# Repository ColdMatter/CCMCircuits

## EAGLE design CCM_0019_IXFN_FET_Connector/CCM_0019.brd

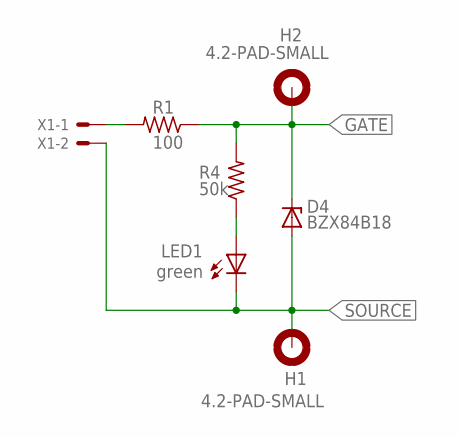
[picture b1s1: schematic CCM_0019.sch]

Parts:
D4: BZX84B18; SOT23
H1, H2: 4.2-PAD-SMALL
LED1: green; CHIPLED_0603
R1: 100; 0603
R4: 50k; 0603
X1: 22-23-2021

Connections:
GATE: D4.3 (C), H2.B4,2, R1.1, R4.2
unnamed: LED1.A, R4.1
unnamed: R1.2, X1.1
SOURCE: D4.1 (A), H1.B4,2, LED1.C, X1.2

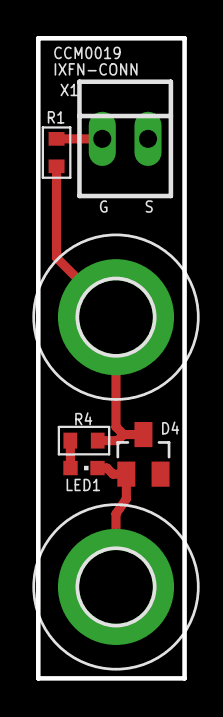
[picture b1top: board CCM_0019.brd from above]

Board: 2 copper layers, 8.1 x 35.6 mm, 7 parts (0 on the bottom side), 4 nets.

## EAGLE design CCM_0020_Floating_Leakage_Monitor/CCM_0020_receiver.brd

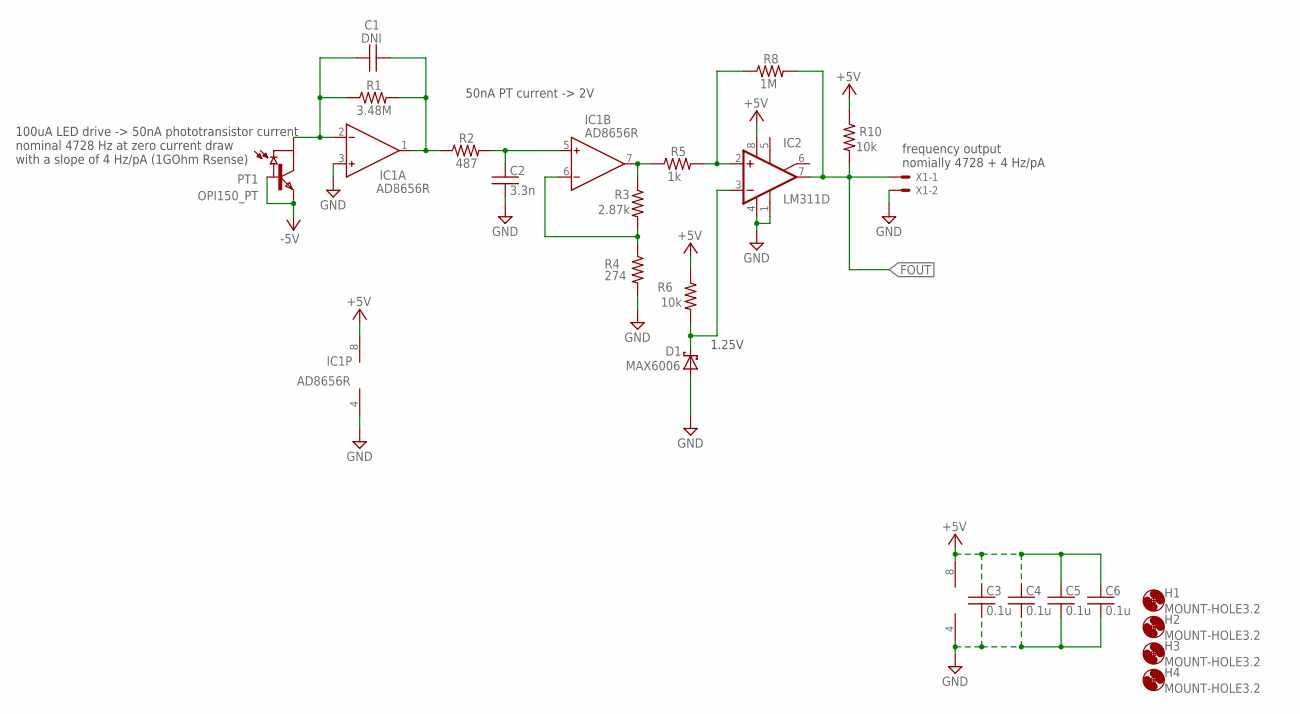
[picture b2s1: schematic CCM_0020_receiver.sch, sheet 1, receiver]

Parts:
C1: DNI; 0603
C2: 3.3n; 0603
C3, C4, C5, C6: 0.1u; 0603
D1: MAX6006; SOT23
H1, H2, H3, H4: MOUNT-HOLE3.2; 3,2
IC1: AD8656R; SO8
IC2: LM311D; SO08
IC3: LT1495; SO08
PT1: OPI150_PT; OPI150_PHOTOTRANSISTOR
R1: 3.48M; 0603
R2: 487; 0603
R3: 2.87k; 0603
R4: 274; 0603
R5: 1k; 0603
R6, R10: 10k; 0603
R8: 1M; 0603
X1: 22-23-2021

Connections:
+5V: C3.1, C4.1, C5.1, C6.1, IC1.8 (V+), IC2.8 (V+), IC3.8 (V+), R6.1, R10.1; also elsewhere on the board
-5V: PT1.P4 (BASE), PT1.P5 (EMITTER)
FOUT: IC2.7 (OUT), R8.2, R10.2, X1.1; also elsewhere on the board
GND: C2.2, C3.2, C4.2, C5.2, C6.2, D1.2 (A), IC1.3 (IN+), IC1.4 (V-), IC2.1 (GND), IC2.4 (V-), IC3.4 (V-), R4.2, X1.2; also elsewhere on the board
unnamed: C1.1, IC1.2 (IN-), PT1.P3 (COLLECTOR), R1.1
unnamed: C2.1, IC1.5 (IN+), R2.2
unnamed: C1.2, IC1.1 (OUT), R1.2, R2.1
unnamed: IC1.6 (IN-), R3.2, R4.1
unnamed: IC1.7 (OUT), R3.1, R5.1
unnamed: IC2.2 (+IN), R5.2, R8.1
unnamed: D1.1 (C), IC2.3 (-IN), R6.2

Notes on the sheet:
100uA LED drive -> 50nA phototransistor current nominal 4728 Hz at zero current draw with a slope of 4 Hz/pA (1GOhm Rsense)
50nA PT current -> 2V
1.25V
frequency output nomially 4728 + 4 Hz/pA

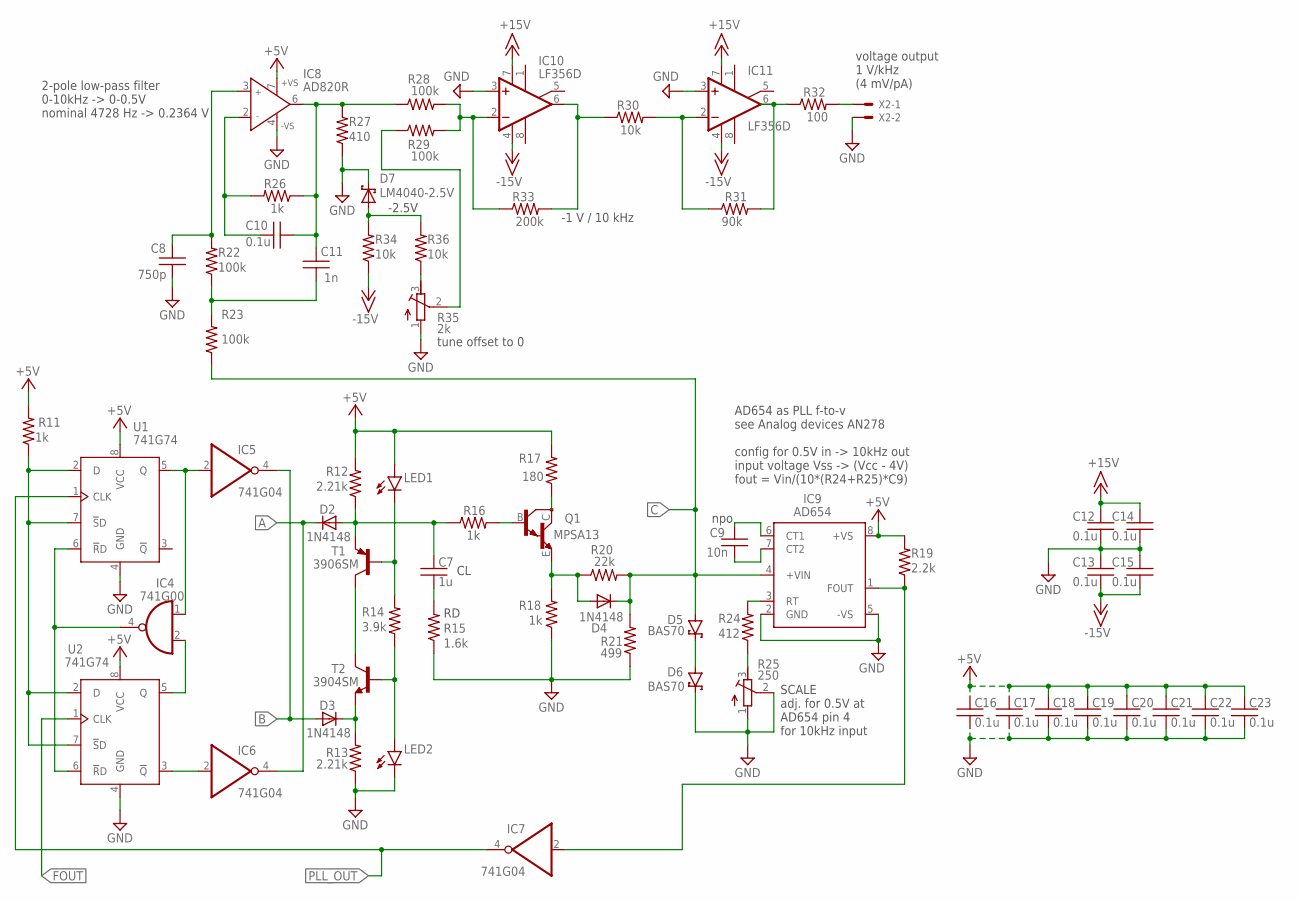
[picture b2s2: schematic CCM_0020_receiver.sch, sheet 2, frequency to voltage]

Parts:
C7: 1u; 0603
C8: 750p; 0603
C9: 10n; 0603
C10, C12, C13, C14, C15, C16, C17, C18, C19, C20, C21, C22, C23: 0.1u; 0603
C11: 1n; 0603
D2, D3, D4: 1N4148; SOD323_ST
D5, D6: BAS70; SOT23
D7: LM4040-2.5V; SOT23
IC4: 741G00; SOT23-5
IC5, IC6, IC7: 741G04; SOT23-5
IC8: AD820R; SO8
IC9: AD654; SO08
IC10, IC11: LF356D; SO08
LED1, LED2: LEDCHIP-LED0603; CHIP-LED0603
Q1: MPSA13; SOT23-BEC
R11, R16, R18, R26: 1k; 0603
R12, R13: 2.21k; 0603
R14: 3.9k; 0603
R15: 1.6k; 0603
R17: 180; 0603
R19: 2.2k; 0603
R20: 22k; 0603
R21: 499; 0603
R22, R23, R28, R29: 100k; 0603
R24: 412; 0603
R25: 250; RTRIM64Y
R27: 410; 0603
R30, R34, R36: 10k; 0603
R31: 90k; 0603
R32: 100; 0603
R33: 200k; 0603
R35: 2k; RTRIM64Y
T1: 3906SM; SOT23-BEC
T2: 3904SM; SOT23
U1, U2: 741G74; TSSOP8
X2: 22-23-2021

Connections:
+5V: C16.1, C17.1, C18.1, C19.1, C20.1, C21.1, C22.1, C23.1, IC8.7 (+VS), IC9.8 (+VS), LED1.A, R11.2, R12.2, R17.2, R19.2, U1.8 (VCC), U2.8 (VCC); also elsewhere on the board
+15V: C12.2, C14.2, IC10.7 (V+), IC11.7 (V+)
-15V: C13.1, C15.1, IC10.4 (V-), IC11.4 (V-), R34.1
A: D2.C, IC6.4 (O)
B: D3.A, IC5.4 (O)
C: D4.C, D5.1 (A), IC9.4 (+VIN), R20.2, R21.2, R23.1
FOUT: U2.1 (CLK); also elsewhere on the board
GND: C8.1, C12.1, C13.2, C14.1, C15.2, C16.2, C17.2, C18.2, C19.2, C20.2, C21.2, C22.2, C23.2, D6.3 (C), D7.1 (C), IC4.3 (GND), IC5.3 (GND), IC6.3 (GND), IC7.3 (GND), IC8.4 (-VS), IC9.2 (GND), IC9.5 (-VS), IC10.3 (+IN), IC11.3 (+IN), LED2.C, R13.1, R15.1, R18.1, R21.1, R25.1 (A), R25.2 (S), R27.1, R35.1 (A), U1.4 (GND), U2.4 (GND), X2.2; also elsewhere on the board
unnamed: C9.1, IC9.6 (CT1)
unnamed: IC4.4 (O), U1.6 (!R!D), U2.6 (!R!D)
unnamed: IC4.2 (I1), U2.5 (Q)
unnamed: R11.1, U1.2 (D), U1.7 (!S!D), U2.2 (D), U2.7 (!S!D)
unnamed: IC6.2 (I), U2.3 (!Q)
unnamed: C11.1, R22.1, R23.2
unnamed: IC4.1 (I0), IC5.2 (I), U1.5 (Q)
unnamed: C8.2, IC8.3 (IN+), R22.2
unnamed: C9.2, IC9.7 (CT2)
unnamed: R24.1, R25.3 (E)
unnamed: D5.3 (C), D6.1 (A)
unnamed: C7.1, D2.A, R12.1, R16.1, T1.E
unnamed: D3.C, R13.2, T2.2 (E)
unnamed: T1.C, T2.3 (C)
unnamed: LED1.C, R14.2, T1.B
unnamed: LED2.A, R14.1, T2.1 (B)
unnamed: C7.2, R15.2
unnamed: Q1.C, R17.1
unnamed: Q1.B, R16.2
unnamed: D4.A, Q1.E, R18.2, R20.1
unnamed: IC9.3 (RT), R24.2
unnamed: IC7.2 (I), IC9.1 (FOUT), R19.1
unnamed: C10.2, C11.2, IC8.6 (OUT), R26.1, R27.2, R28.1
unnamed: C10.1, IC8.2 (IN-), R26.2
unnamed: IC10.2 (-IN), R28.2, R29.2, R33.1
unnamed: IC11.6 (OUT), R31.2, R32.1
unnamed: IC11.2 (-IN), R30.2, R31.1
unnamed: R32.2, X2.1
unnamed: IC10.6 (OUT), R30.1, R33.2
unnamed: D7.2 (A), R34.2, R36.2
unnamed: R29.1, R35.2 (S)
unnamed: R35.3 (E), R36.1
PLL_OUT: IC7.4 (O), U1.1 (CLK)
VCC: IC4.5 (VCC), IC5.5 (VCC), IC6.5 (VCC), IC7.5 (VCC)

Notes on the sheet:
npo
SCALE adj. for 0.5V at AD654 pin 4 for 10kHz input
2-pole low-pass filter 0-10kHz -> 0-0.5V nominal 4728 Hz -> 0.2364 V
AD654 as PLL f-to-v see Analog devices AN278 config for 0.5V in -> 10kHz out input voltage Vss -> (Vcc - 4V) fout = Vin/(10*(R24+R25)*C9)
-2.5V
tune offset to 0
-1 V / 10 kHz
voltage output 1 V/kHz (4 mV/pA)

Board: 2 copper layers, 89 parts (0 on the bottom side), 50 nets, no tracks yet.

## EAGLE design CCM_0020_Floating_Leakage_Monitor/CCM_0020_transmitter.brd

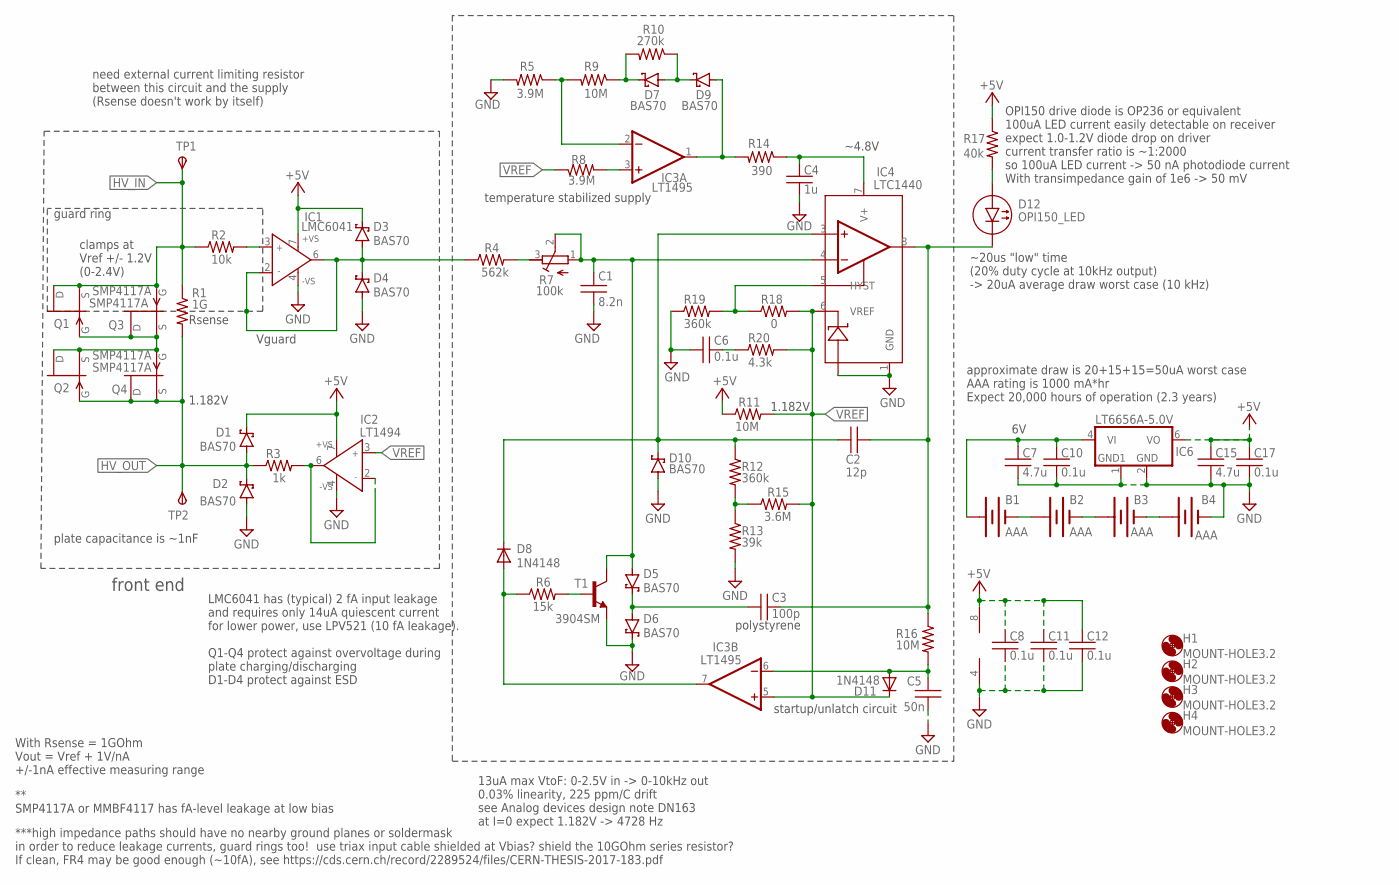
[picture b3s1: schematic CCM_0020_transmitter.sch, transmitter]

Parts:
B1, B2, B3, B4: AAA; AAA_SM
C1: 8.2n; 0603
C2: 12p; 0603
C3: 100p; 0603
C4: 1u; 0603
C5: 50n; 0603
C6, C8, C10, C11, C12, C17: 0.1u; 0603
C7, C15: 4.7u; 0603
D1, D2, D3, D4, D5, D6, D7, D9, D10: BAS70; SOT23
D8, D11: 1N4148; SOD323_ST
D12: OPI150_LED
H1, H2, H3, H4: MOUNT-HOLE3.2; 3,2
IC1: LMC6041; SO08
IC2: LT1494; SO08
IC3: LT1495; SO08
IC4: LTC1440; SO8
IC6: LT6656A-5.0V; SOT23-6
Q1, Q2, Q3, Q4: SMP4117A; SOT23
R1: 1G; 2512
R2: 10k; 0603
R3: 1k; 0603
R4: 562k; 0603
R5, R8: 3.9M; 0603
R6: 15k; 0603
R7: 100k; RTRIM64Y
R9, R11, R16: 10M; 0603
R10: 270k; 0603
R12, R19: 360k; 0603
R13: 39k; 0603
R14: 390; 0603
R15: 3.6M; 0603
R17: 40k; 0603
R18: 0; 0603
R20: 4.3k; 0603
T1: 3904SM; SOT23
TP1, TP2: TPSPAD1-17; P1-17

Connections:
+5V: C8.1, C11.1, C12.1, C15.1, C17.1, D1.3 (C), D3.3 (C), IC1.7 (+VS), IC2.7 (+VS), IC3.8 (V+), IC6.6 (VO), R11.1, R17.1
GND: B4.-, C1.2, C4.2, C5.2, C6.1, C7.2, C8.2, C10.2, C11.2, C12.2, C15.2, C17.2, D2.1 (A), D4.1 (A), D6.3 (C), D10.1 (A), IC1.4 (-VS), IC2.4 (-VS), IC3.4 (V-), IC4.1 (GND), IC4.2 (V-), IC6.1 (GND1), IC6.2 (GND), R5.2, R13.2, R19.1, T1.2 (E)
HV_IN: Q1.1 (D), Q1.2 (S), Q3.3 (G), R1.1, R2.1, TP1.TP
HV_IN1: Q1.3 (G), Q2.1 (D), Q2.2 (S), Q3.1 (D), Q3.2 (S), Q4.3 (G)
HV_OUT: D1.1 (A), D2.3 (C), Q2.3 (G), Q4.1 (D), Q4.2 (S), R1.2, R3.1, TP2.TP
unnamed: D3.1 (A), D4.3 (C), IC1.2 (IN-), IC1.6 (OUT), R4.1
unnamed: IC4.5 (HYST), R18.1, R19.2
unnamed: D12.P$1 (1(A)), R17.2
unnamed: B1.-, B2.+
unnamed: C6.2, R20.1
unnamed: C5.1, D11.A, IC3.6 (-IN), R16.2
unnamed: IC1.3 (IN+), R2.2
unnamed: R4.2, R7.3 (E)
unnamed: C1.1, D5.1 (A), IC4.4 (-IN), R7.1 (A), R7.2 (S), T1.3 (C)
unnamed: C3.1, D5.3 (C), D6.1 (A)
unnamed: R6.2, T1.1 (B)
unnamed: D8.A, IC3.7 (OUT), R6.1
unnamed: R12.2, R13.1, R15.1
unnamed: C2.1, D8.C, D10.3 (C), IC4.3 (+IN), R12.1
unnamed: D7.1 (A), D9.3 (C), R10.1
unnamed: D7.3 (C), R9.1, R10.2
unnamed: IC3.2 (-IN), R5.1, R9.2
unnamed: B1.+, C7.1, C10.1, IC6.4 (VI)
unnamed: D9.1 (A), IC3.1 (OUT), R14.2
unnamed: C4.1, IC4.7 (V+), R14.1
unnamed: IC3.3 (+IN), R8.2
unnamed: B2.-, B3.+
unnamed: B3.-, B4.+
unnamed: IC2.2 (IN-), IC2.6 (OUT), R3.2
VREF: D11.C, IC2.3 (IN+), IC3.5 (+IN), IC4.6 (VREF), R8.1, R11.2, R15.2, R18.2, R20.2
VTOF_OUTPUT: C2.2, C3.2, D12.P$2 (2(C)), IC4.8 (OUT), R16.1

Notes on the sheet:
** SMP4117A or MMBF4117 has fA-level leakage at low bias
plate capacitance is ~1nF
With Rsense = 1GOhm Vout = Vref + 1V/nA +/-1nA effective measuring range
***high impedance paths should have no nearby ground planes or soldermask in order to reduce leakage currents, guard rings too! use triax input cable shielded at Vbias? shield the 10GOhm series resistor? If clean, FR4 may be good enough (~10fA), see https://cds.cern.ch/record/2289524/files/CERN-THE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
polystyrene
front end
13uA max VtoF: 0-2.5V in -> 0-10kHz out 0.03% linearity, 225 ppm/C drift see Analog devices design note DN163 at I=0 expect 1.182V -> 4728 Hz
1.182V
clamps at Vref +/- 1.2V (0-2.4V)
approximate draw is 20+15+15=50uA worst case AAA rating is 1000 mA*hr Expect 20,000 hours of operation (2.3 years)
guard ring
~20us "low" time (20% duty cycle at 10kHz output) -> 20uA average draw worst case (10 kHz)
OPI150 drive diode is OP236 or equivalent 100uA LED current easily detectable on receiver expect 1.0-1.2V diode drop on driver current transfer ratio is ~1:2000 so 100uA LED current -> 50 nA photodiode current With transimpedance gain of 1e6 -> 50 mV
Vguard
LMC6041 has (typical) 2 fA input leakage and requires only 14uA quiescent current for lower power, use LPV521 (10 fA leakage). Q1-Q4 protect against overvoltage during plate charging/discharging D1-D4 protect against ESD
need external current limiting resistor between this circuit and the supply (Rsense doesn't work by itself)
Rsense
temperature stabilized supply
startup/unlatch circuit
~4.8V

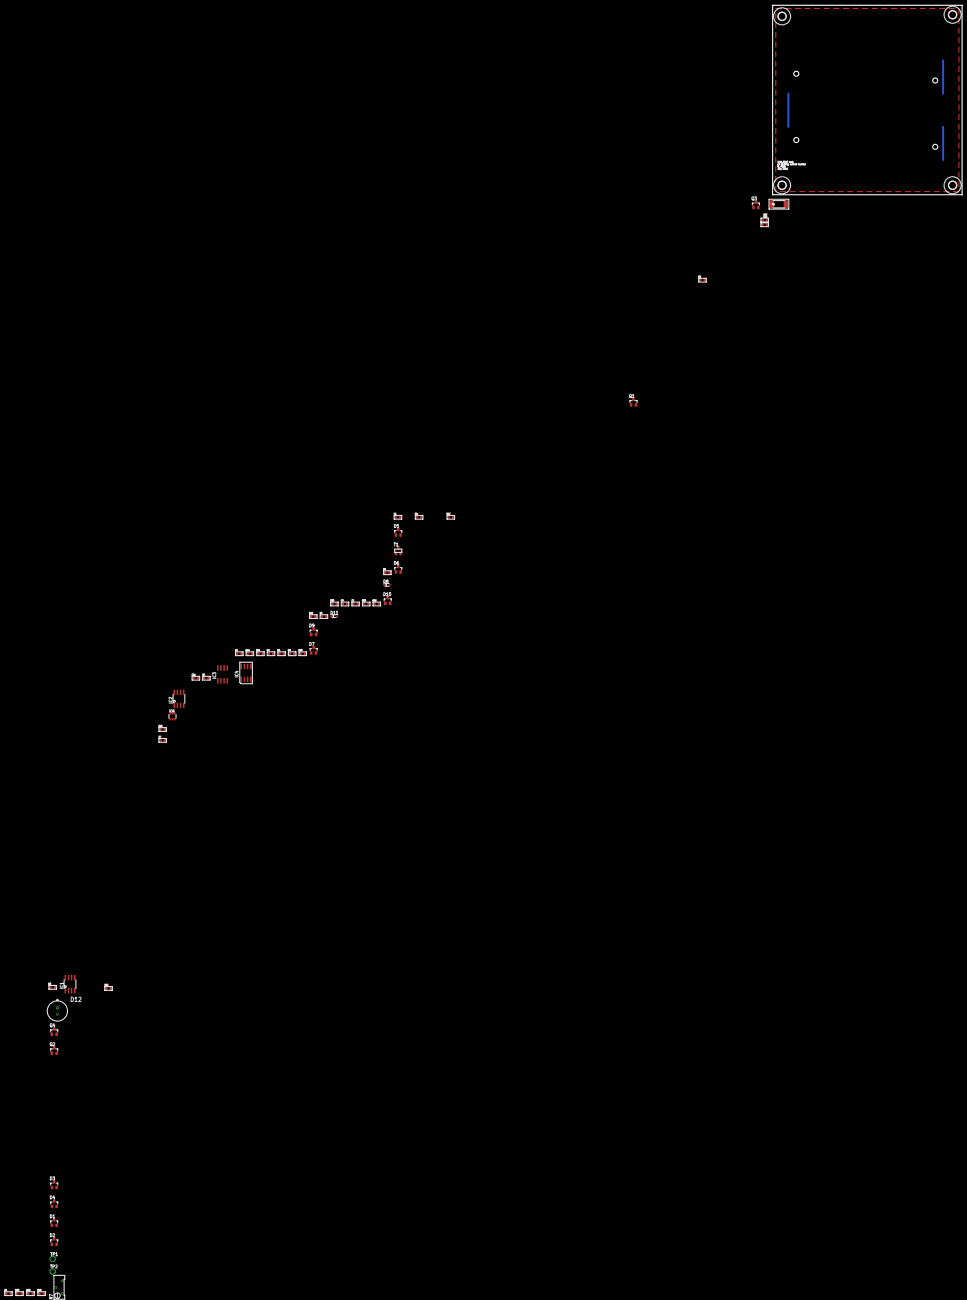
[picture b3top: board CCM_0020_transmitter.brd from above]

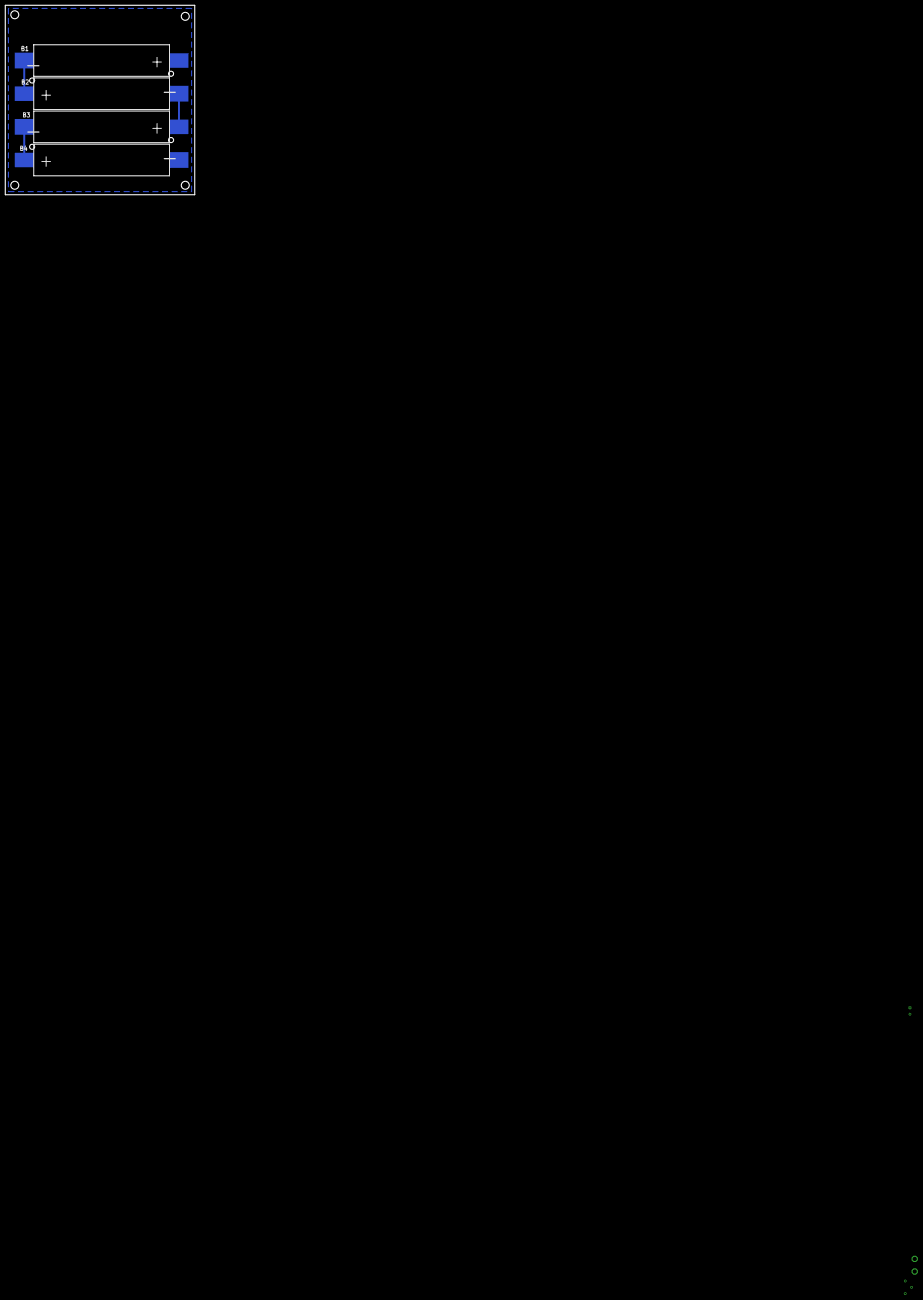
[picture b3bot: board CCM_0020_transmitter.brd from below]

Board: 2 copper layers, 76.2 x 76.2 mm, 65 parts (4 on the bottom side), 31 nets.

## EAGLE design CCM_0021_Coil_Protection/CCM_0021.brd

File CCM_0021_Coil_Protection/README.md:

# CCM_0021 Coil Protection
     
This circuit is designed to provide some level of protection for coils, particularly useful for those installed in vacuum where a melted coil represents a serious annoyance.  It features an adjustable soft current limit (by clamping a control voltage) and an adjustable hard energy limit (by opening an interlock and disabling the power supply).  The latter feature is obtained by integrating the dissipated power (roughly) and comparing to a setpoint.  

## Design Resources

## Design Notes

## Known Issues

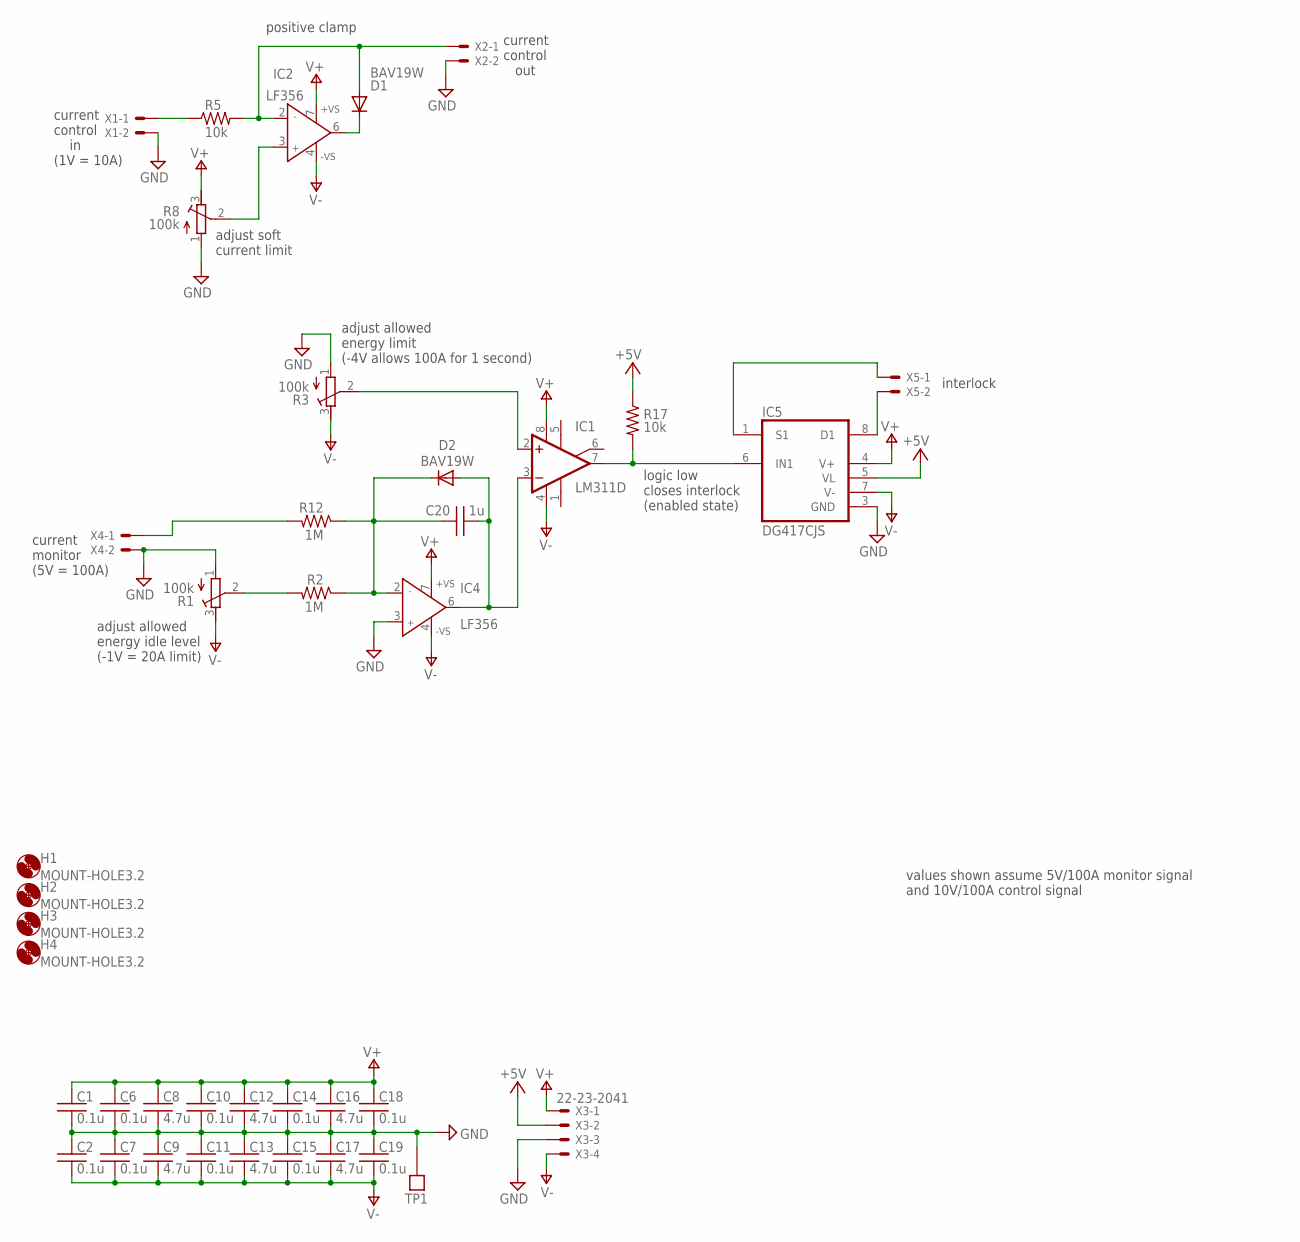
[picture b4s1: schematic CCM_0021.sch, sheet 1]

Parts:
C1, C2, C6, C7, C10, C11, C14, C15, C18, C19: 0.1u; 0603
C8, C9, C12, C13, C16, C17: 4.7u; 0603
C20: 1u; 0603
D1, D2: BAV19W; SOD123
H1, H2, H3, H4: MOUNT-HOLE3.2; 3,2
IC1: LM311D; SO08
IC2, IC4: LF356; SO8
IC5: DG417CJS; SO8
R1, R3, R8: 100k; RTRIM3296W
R2, R12: 1M; 0603
R5, R17: 10k; 0603
TP1: TESTPOINT
X1, X2, X4, X5: 22-23-2021
X3: 22-23-2041

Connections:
+5V: IC5.5 (VL), R17.1, X3.2
GND: C1.2, C2.1, C6.2, C7.1, C8.2, C9.1, C10.2, C11.1, C12.2, C13.1, C14.2, C15.1, C16.2, C17.1, C18.2, C19.1, IC4.3 (IN+), IC5.3 (GND), R1.1 (A), R3.1 (A), R8.1 (A), TP1.P$1, X1.2, X2.2, X3.3, X4.2
unnamed: R12.2, X4.1
unnamed: R1.2 (S), R2.2
unnamed: C20.1, D2.A, IC1.3 (-IN), IC4.6 (OUT)
unnamed: IC1.2 (+IN), R3.2 (S)
unnamed: IC1.7 (OUT), IC5.6 (IN1), R17.2
unnamed: IC5.1 (S1), X5.1
unnamed: IC5.8 (D1), X5.2
unnamed: D1.C, IC2.6 (OUT)
unnamed: IC2.3 (IN+), R8.2 (S)
unnamed: R5.1, X1.1
unnamed: D1.A, IC2.2 (IN-), R5.2, X2.1
unnamed: C20.2, D2.C, IC4.2 (IN-), R2.1, R12.1
V+: C1.1, C6.1, C8.1, C10.1, C12.1, C14.1, C16.1, C18.1, IC1.8 (V+), IC2.7 (+VS), IC4.7 (+VS), IC5.4 (V+), R8.3 (E), X3.1
V-: C2.2, C7.2, C9.2, C11.2, C13.2, C15.2, C17.2, C19.2, IC1.4 (V-), IC2.4 (-VS), IC4.4 (-VS), IC5.7 (V-), R1.3 (E), R3.3 (E), X3.4

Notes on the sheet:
current control in (1V = 10A)
positive clamp
adjust soft current limit
current control out
current monitor (5V = 100A)
adjust allowed energy idle level (-1V = 20A limit)
values shown assume 5V/100A monitor signal and 10V/100A control signal
adjust allowed energy limit (-4V allows 100A for 1 second)
interlock
logic low closes interlock (enabled state)

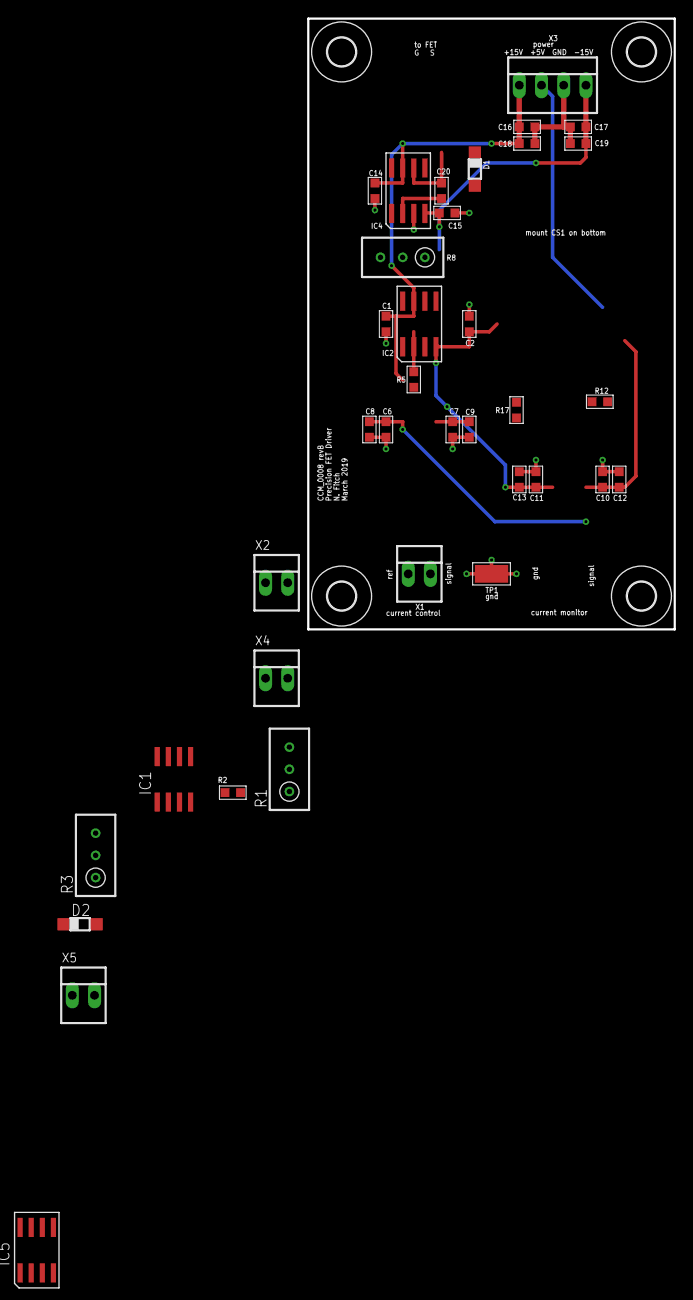
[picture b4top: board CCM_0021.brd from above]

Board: 2 copper layers, 41.9 x 69.8 mm, 40 parts (0 on the bottom side), 16 nets.

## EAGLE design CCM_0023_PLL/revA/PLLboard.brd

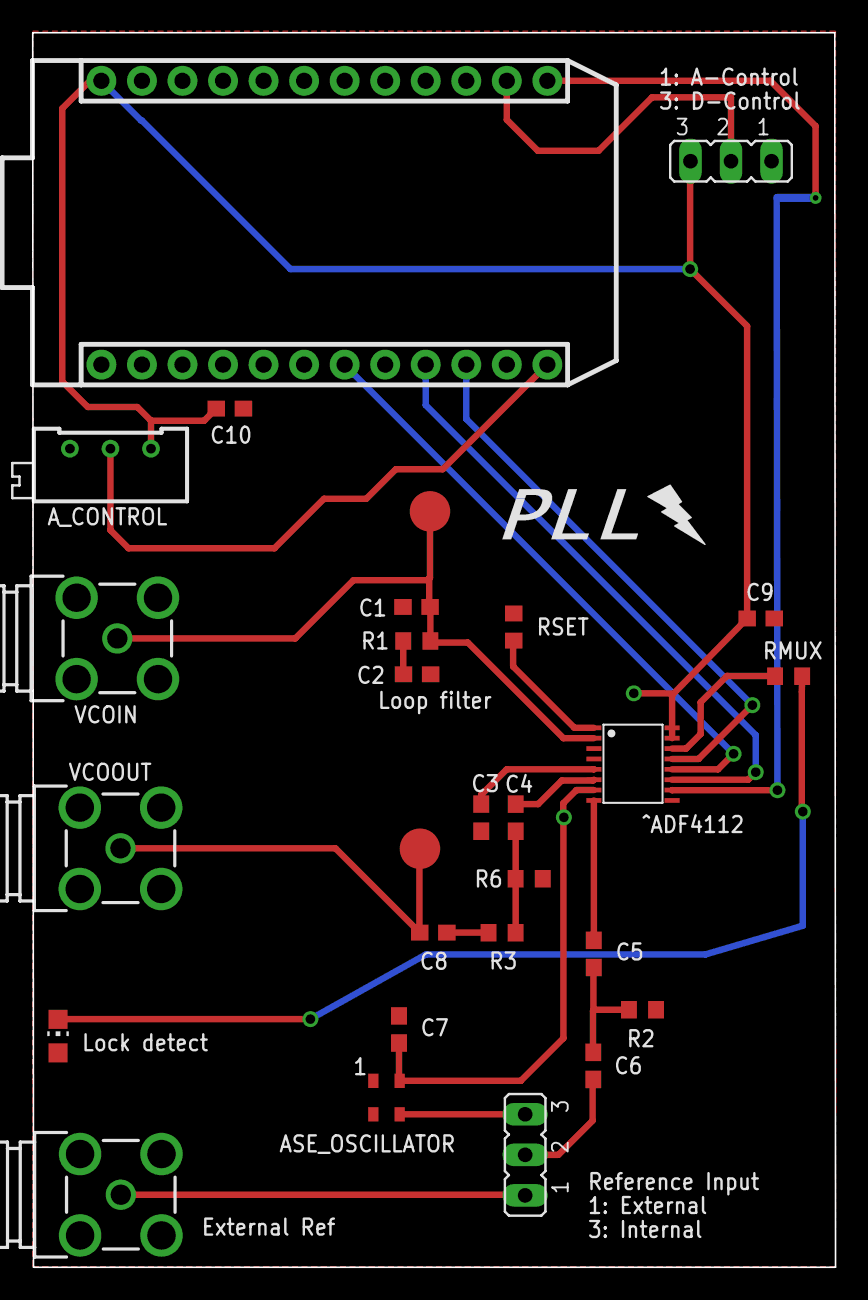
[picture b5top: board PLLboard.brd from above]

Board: 2 copper layers, 50.3 x 77.3 mm, 28 parts (0 on the bottom side), 24 nets.

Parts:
ADF4112: ADF4112
ASE_OSCILLATOR: ASE
A_CONTROL: RTRIM64X
C1: 270p; C0603
C2: 1.20n; C0603
C3, C4, C8: 100p; C0603
C5, C6: 1n; C0603
C7, C9, C10: 0.1u; C0603
EXTERNAL_REFIN: BU-SMA-G
JP1, JP2: JP2
LED1: CHIP-LED0805
MICROCONTOLLER: PHOTON_WITH_HEADERS; PHOTON
R1: 15k; R0603
R2, R6: 51; R0603
R3: 18; R0603
RMUX: 1k; R0603
RSET: 4.7k; R0603
VCOIN: BU-SMA-G
VCOOUT: BU-SMA-G
VCO_IN: PTR1B2,54; B2,54
VCO_OUT: PTR1B2,54; B2,54

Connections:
GND: ADF4112.3, ADF4112.4, ADF4112.9, ASE_OSCILLATOR.2, A_CONTROL.3, C1.2, C2.1, C3.1, C7.1, C9.1, C10.1, EXTERNAL_REFIN.2, EXTERNAL_REFIN.3, EXTERNAL_REFIN.4, EXTERNAL_REFIN.5, JP1.1, LED1.A, MICROCONTOLLER.2, MICROCONTOLLER.21, R2.1, R6.1, RSET.2, VCOIN.2, VCOIN.3, VCOIN.4, VCOIN.5, VCOOUT.2, VCOOUT.3, VCOOUT.4, VCOOUT.5
unnamed: ADF4112.12, MICROCONTOLLER.7
unnamed: ADF4112.11, MICROCONTOLLER.9
unnamed: ADF4112.13, MICROCONTOLLER.10
unnamed: ADF4112.1, RSET.1
unnamed: C2.2, R1.1
unnamed: EXTERNAL_REFIN.1, JP2.1
unnamed: ASE_OSCILLATOR.3, JP2.3
unnamed: ADF4112.8, C5.1
unnamed: C5.2, C6.1, R2.2
unnamed: ADF4112.5, C3.2
unnamed: ADF4112.6, C4.1
unnamed: C8.1, VCOOUT.1, VCO_OUT.TP
unnamed: A_CONTROL.2, MICROCONTOLLER.12
unnamed: JP1.2, MICROCONTOLLER.14
unnamed: C8.2, R3.2
unnamed: C4.2, R3.1, R6.2
unnamed: ADF4112.14, RMUX.2
unnamed: LED1.C, RMUX.1
unnamed: ADF4112.15, ADF4112.16, A_CONTROL.1, C9.2, C10.2, JP1.3, MICROCONTOLLER.24
unnamed: ADF4112.10, MICROCONTOLLER.13
unnamed: ADF4112.2, C1.1, R1.2, VCOIN.1, VCO_IN.TP
unnamed: C6.2, JP2.2
S$1: ADF4112.7, ASE_OSCILLATOR.4, C7.2
